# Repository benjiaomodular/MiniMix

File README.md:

# MiniMix
A 4-channel mixer for Eurorack module synth.

## Versions

### v1.0
- Issue: Faders were upside-down
- Issue: Input 2 wasn't connected to ground

### v1.1
- Issue: Input 2 wasn't connected to ground

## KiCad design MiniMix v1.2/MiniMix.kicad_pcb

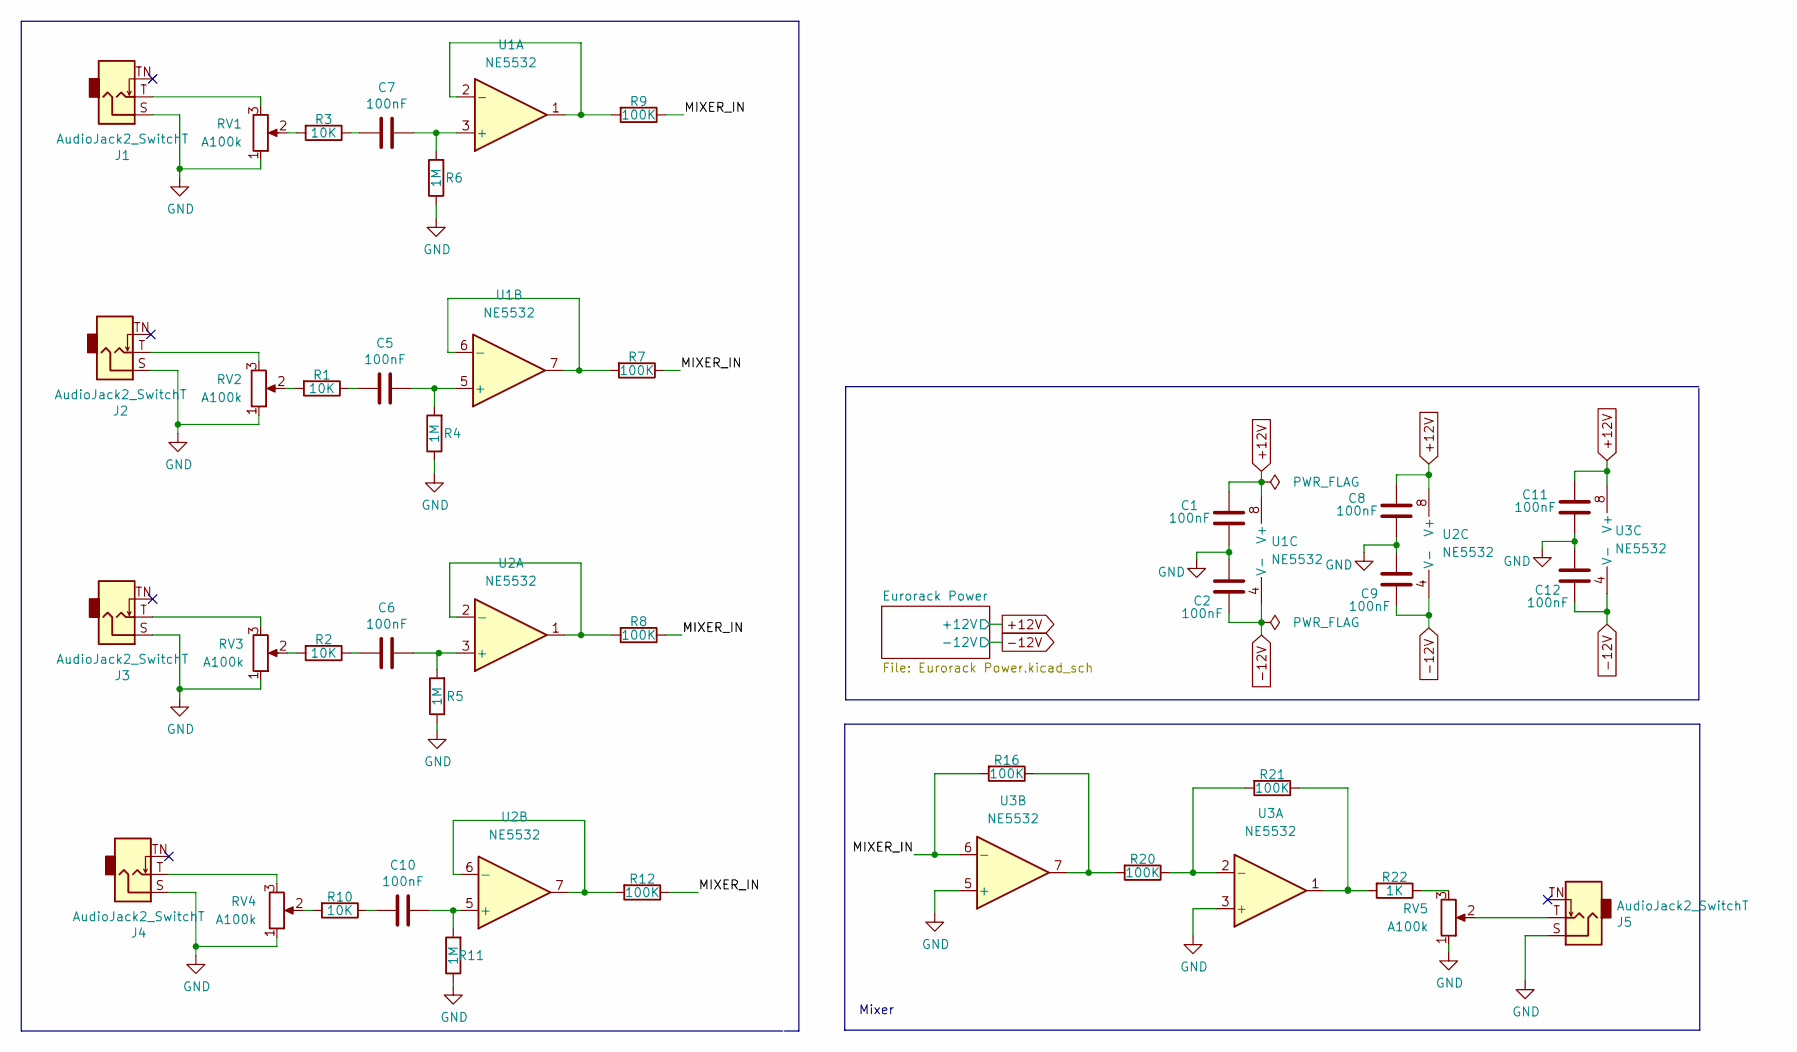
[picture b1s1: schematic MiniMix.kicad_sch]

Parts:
C1, C2, C5, C6, C7, C8, C9, C10, C11, C12: 100nF; C_0603_1608Metric_Pad1.08x0.95mm_HandSolder; Manufacturers Part Numb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 CC0603JRX7R9BB104
J1, J2, J3, J4, J5: AudioJack2_SwitchT; AudioJack_3.5mm; Manufacturers Part Numb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 PJ-3001F
R1, R2, R3, R10: 10K; R_0603_1608Metric_Pad0.98x0.95mm_HandSolder; Manufacturers Part Numb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 AC0603FR-0710KL
R4, R5, R6, R11: 1M; R_0603_1608Metric_Pad0.98x0.95mm_HandSolder; Manufacturers Part Numb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 RC0603FR-071ML
R7, R8, R9, R12, R16, R20, R21: 100K; R_0603_1608Metric_Pad0.98x0.95mm_HandSolder; Manufacturers Part Numb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 RC0603FR-07100KL
R22: 1K; R_0603_1608Metric_Pad0.98x0.95mm_HandSolder; Manufacturers Part Numb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 RC0603FR-071KL
RV1, RV2, RV3, RV4: A100k; Potentiometer_Bourns_PTA4543_Single_Slide; Manufacturers Part Numb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 PTA4553-2015DPA104
RV5: A100k; Potentiometer_RV09; Manufacturers Part Numb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 RV09AF-40-20K-A100K
U1, U2, U3: NE5532; SOIC-8_3.9x4.9mm_P1.27mm; Manufacturers Part Numb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 NE5532ADR

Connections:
+12V: C1.2, C8.2, C11.2, U1.8 (V+), U2.8 (V+), U3.8 (V+); also elsewhere on the board
-12V: C2.1, C9.1, C12.1, U1.4 (V-), U2.4 (V-), U3.4 (V-); also elsewhere on the board
/MIXER_IN: R7.1, R8.1, R9.1, R12.1, R16.2, U3.6 (-)
GND: C1.1, C2.2, C8.1, C9.2, C11.1, C12.2, J1.S, J2.S, J3.S, J4.S, J5.S, R4.1, R5.1, R6.1, R11.1, RV1.1, RV2.1, RV3.1, RV4.1, RV5.1, U3.3 (+), U3.5 (+); also elsewhere on the board
unnamed: C5.1, R4.2, U1.5 (+)
unnamed: C5.2, R1.1
unnamed: C6.1, R5.2, U2.3 (+)
unnamed: C6.2, R2.1
unnamed: C7.1, R6.2, U1.3 (+)
unnamed: C7.2, R3.1
unnamed: C10.1, R11.2, U2.5 (+)
unnamed: C10.2, R10.1
unnamed: J1.T, RV1.3
unnamed: J2.T, RV2.3
unnamed: J3.T, RV3.3
unnamed: J4.T, RV4.3
unnamed: J5.T, RV5.2
unnamed: R1.2, RV2.2
unnamed: R2.2, RV3.2
unnamed: R3.2, RV1.2
unnamed: R7.2, U1.6 (-), U1.7
unnamed: R8.2, U2.1, U2.2 (-)
unnamed: R9.2, U1.1, U1.2 (-)
unnamed: R10.2, RV4.2
unnamed: R12.2, U2.6 (-), U2.7
unnamed: R16.1, R20.2, U3.7
unnamed: R20.1, R21.2, U3.2 (-)
unnamed: R21.1, R22.2, U3.1
unnamed: R22.1, RV5.3

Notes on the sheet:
Mixer

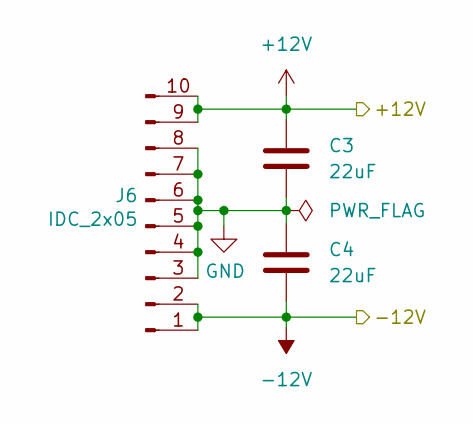
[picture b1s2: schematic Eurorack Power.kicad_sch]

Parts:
C3, C4: 22uF; C_0805_2012Metric_Pad1.18x1.45mm_HandSolder; Manufacturers Part Numb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 GRM21BR61E226ME44L
J6: IDC_2x05; IDC-Header_2x05_P2.54mm_Vertical; Manufacturers Part Numb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 X9555WV-2X05-6TV01; LCSC Part # C706914

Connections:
+12V: C3.1, J6.9, J6.10; also elsewhere on the board
-12V: C4.2, J6.1, J6.2; also elsewhere on the board
GND: C3.2, C4.1, J6.3, J6.4, J6.5, J6.6, J6.7, J6.8; also elsewhere on the board

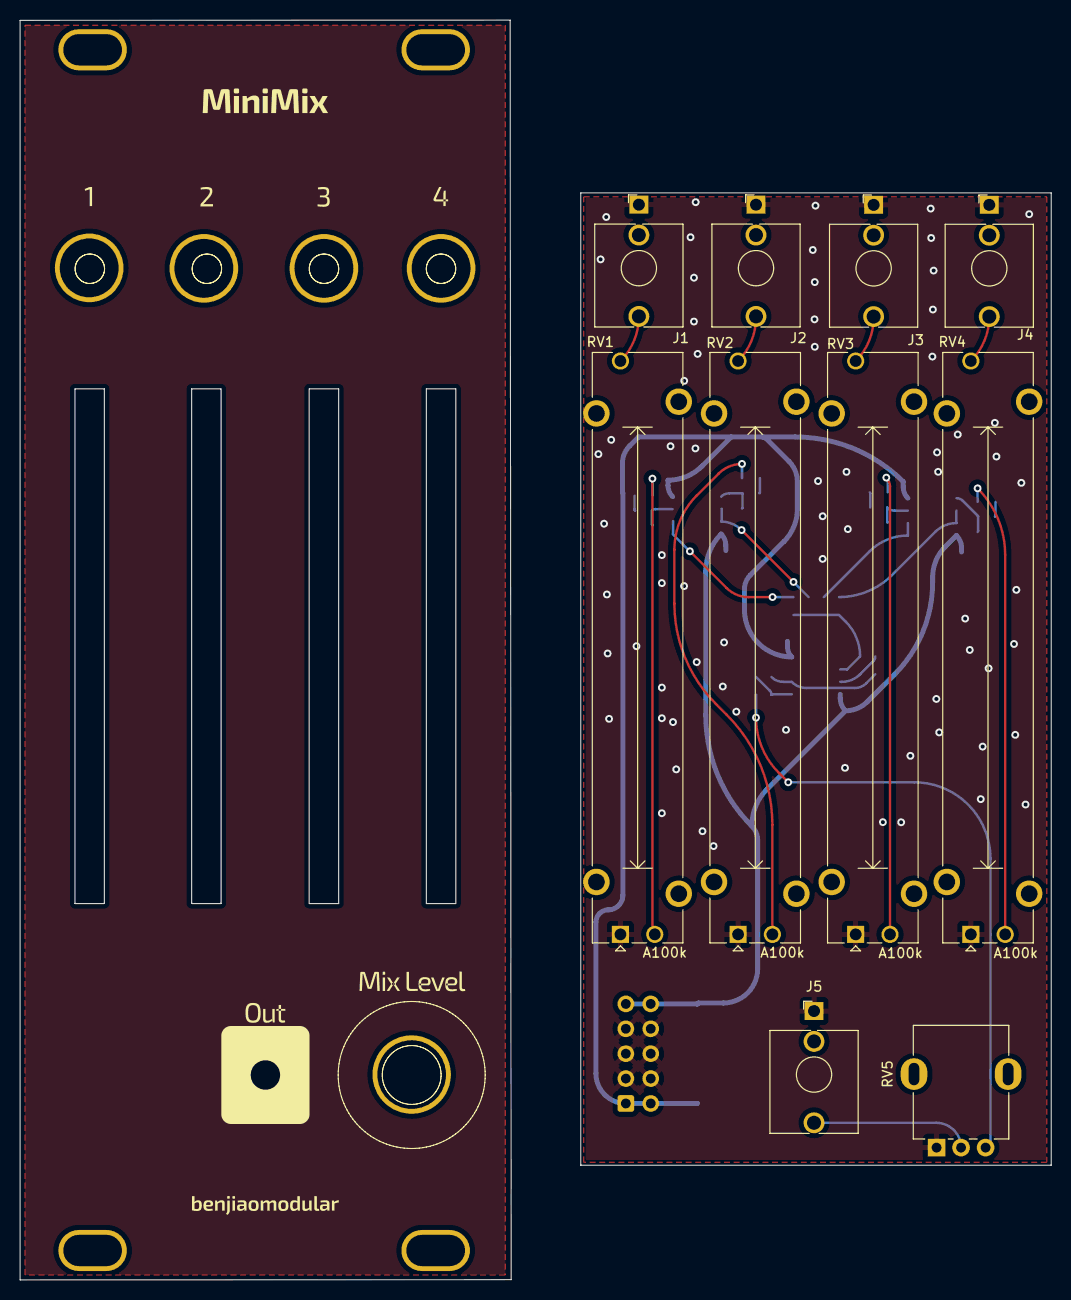
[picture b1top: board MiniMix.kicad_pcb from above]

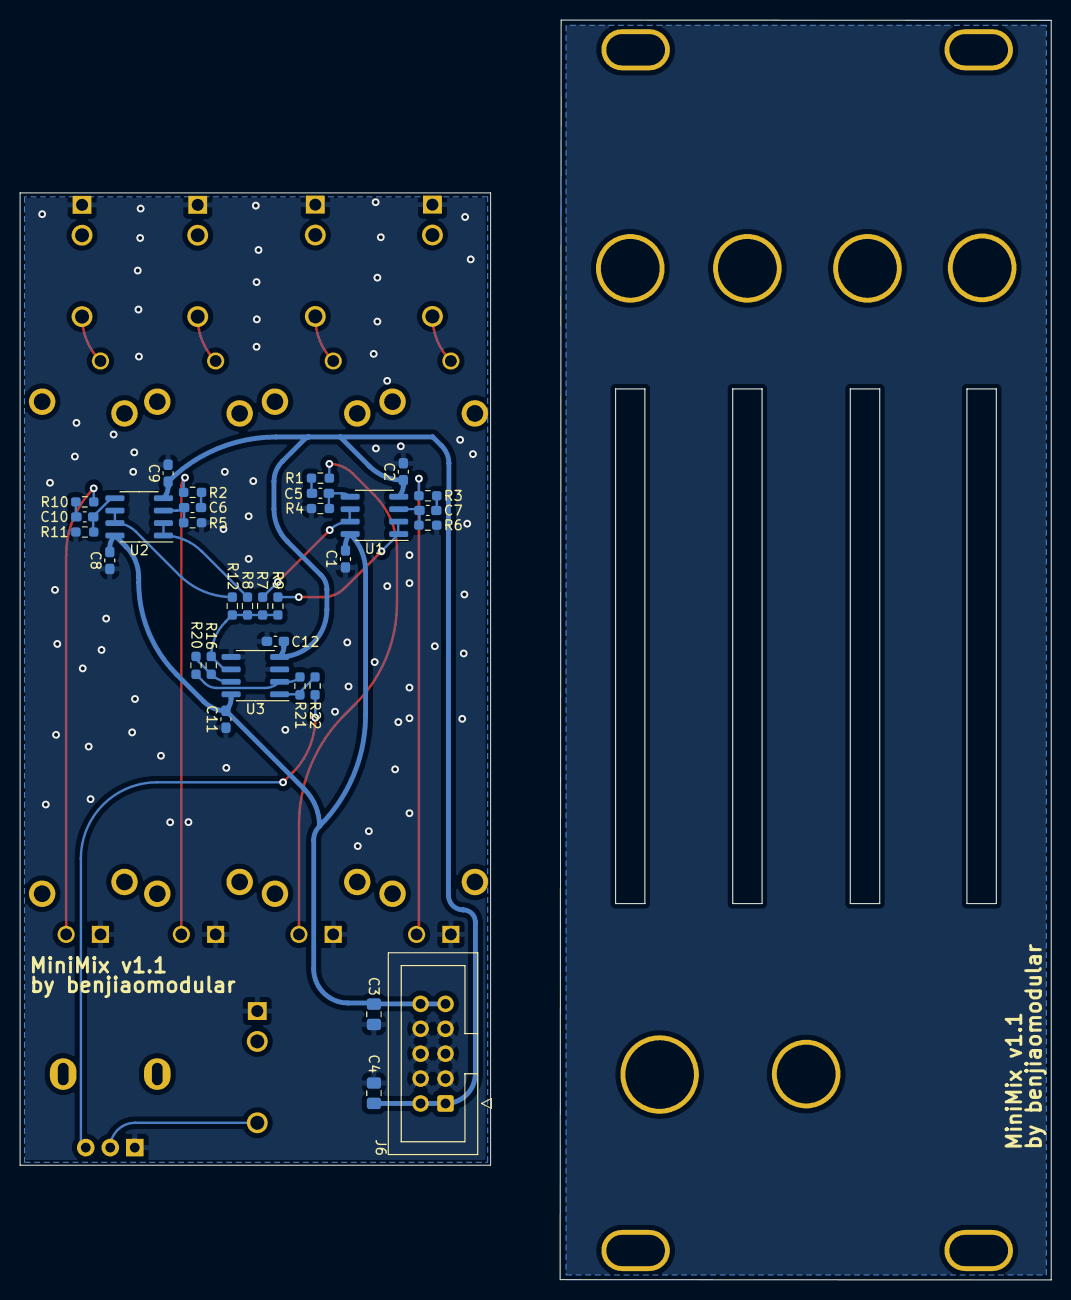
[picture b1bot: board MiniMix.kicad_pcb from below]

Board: 2 copper layers, 48.0 x 99.2 mm, 42 parts (32 on the bottom side), 29 nets.

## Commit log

2023-06-04 Added v1.2
2023-06-10 Updated license
2023-08-17 Added pos files for v1.1
